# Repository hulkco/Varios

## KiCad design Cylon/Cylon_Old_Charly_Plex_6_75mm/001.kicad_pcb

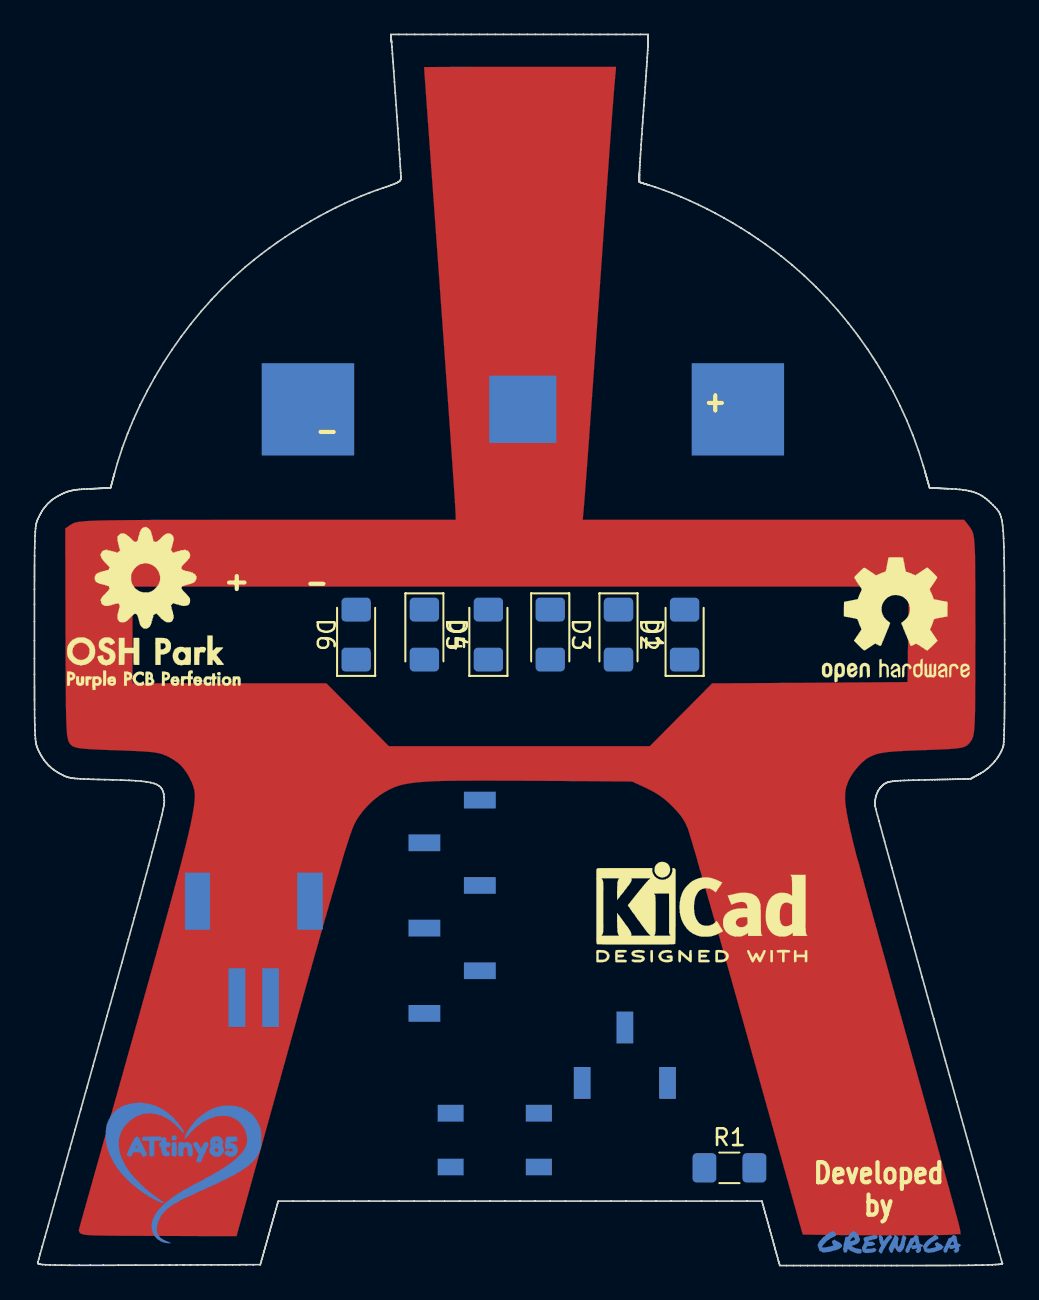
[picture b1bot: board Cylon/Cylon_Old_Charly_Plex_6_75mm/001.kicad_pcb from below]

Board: 2 copper layers, 57.8 x 73.3 mm, 17 parts (15 on the bottom side), 6 nets, no tracks yet.

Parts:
BT1: Battery_Cell; S8211R
D1, D2, D3, D4, D5, D6: LED; LED_1206_3216Metric_Pad1.42x1.75mm_HandSolder
J1: Conn_01x02; JST-S2B-PH-SM4-TB
J2: Conn_01x06_x03; Digispark_SMD_Reverse
R1: R_Small; R_1206_3216Metric_Pad1.42x1.75mm_HandSolder
SW2: SW_Push_Dual; SW_Push_PTS647_4.5mm
U1: PCB; Cylon_001
U2: Firma; firma_Cu_Mask
U3: Oshpark_logo; OSHpark-1-1200
U4: Oshpark_Purple; OSHpark-2-1800
U5: OSHW_Silk; OSHW-Logo2_9.8x8mm_SilkScreen
U6: Love_ATtiny85; Moon_ATtiny85

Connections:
/PB_0: D1.1, D2.2, D5.1, D6.2, J2.1
/PB_1: D1.2, D2.1, D3.1, D4.2, J2.2
/PB_2: J2.3, R1.1, SW2.1, SW2.2
/PB_4: D3.2, D4.1, D5.2, D6.1, J2.5
GND: BT1.2, J1.2, J2.8, SW2.3, SW2.4
VCC: BT1.1, J1.1, J2.9, R1.2

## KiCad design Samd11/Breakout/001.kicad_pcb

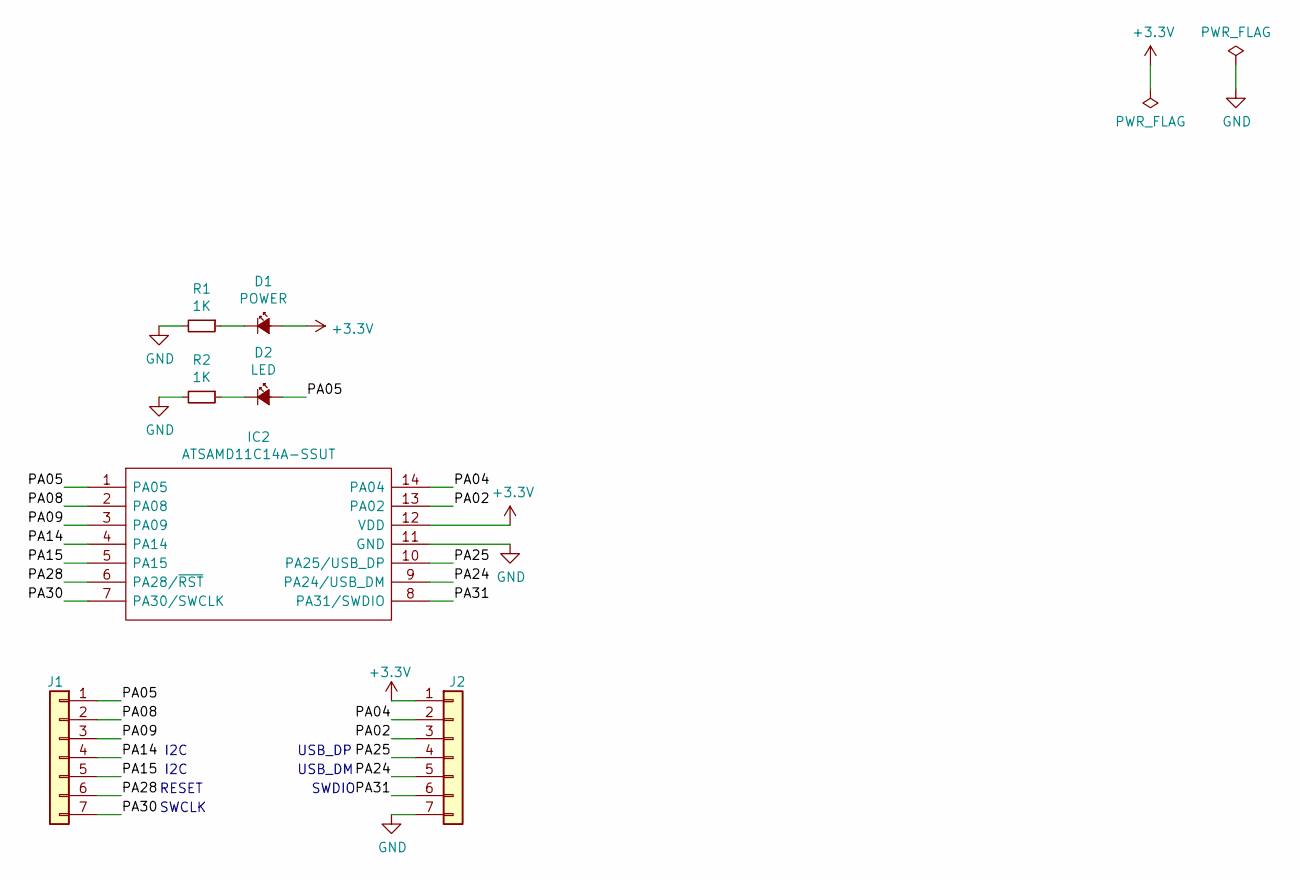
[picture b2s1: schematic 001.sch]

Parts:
D1: POWER; LED_1206_3216Metric_Pad1.42x1.75mm_HandSolder
D2: LED; LED_1206_3216Metric_Pad1.42x1.75mm_HandSolder
IC2: ATSAMD11C14A-SSUT; SOIC127P600X175-14N; Mouser Part Number 556-ATSAMD11C14ASSUT
J1, J2: Conn_01x07; PinHeader_1x07_P2.54mm_Vertical
R1, R2: 1K; R_1206_3216Metric_Pad1.42x1.75mm_HandSolder

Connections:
+3V3: D1.2 (A), IC2.12 (VDD), J2.1
/PA02: IC2.13 (PA02), J2.3
/PA04: IC2.14 (PA04), J2.2
/PA05: D2.2 (A), IC2.1 (PA05), J1.1
/PA08: IC2.2 (PA08), J1.2
/PA09: IC2.3 (PA09), J1.3
/PA14: IC2.4 (PA14), J1.4
/PA15: IC2.5 (PA15), J1.5
/PA24: IC2.9 (PA24/USB_DM), J2.5
/PA25: IC2.10 (PA25/USB_DP), J2.4
/PA28: IC2.6 (PA28/~RST), J1.6
/PA30: IC2.7 (PA30/SWCLK), J1.7
/PA31: IC2.8 (PA31/SWDIO), J2.6
GND: IC2.11 (GND), J2.7, R1.2, R2.2
unnamed: D1.1 (K), R1.1
unnamed: D2.1 (K), R2.1

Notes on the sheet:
SWDIO
SWCLK
RESET
I2C
USB_DM
USB_DP

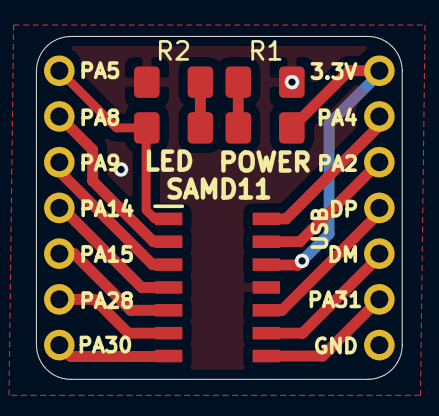
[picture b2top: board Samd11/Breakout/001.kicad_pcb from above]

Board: 2 copper layers, 20.3 x 19.0 mm, 7 parts (0 on the bottom side), 16 nets.

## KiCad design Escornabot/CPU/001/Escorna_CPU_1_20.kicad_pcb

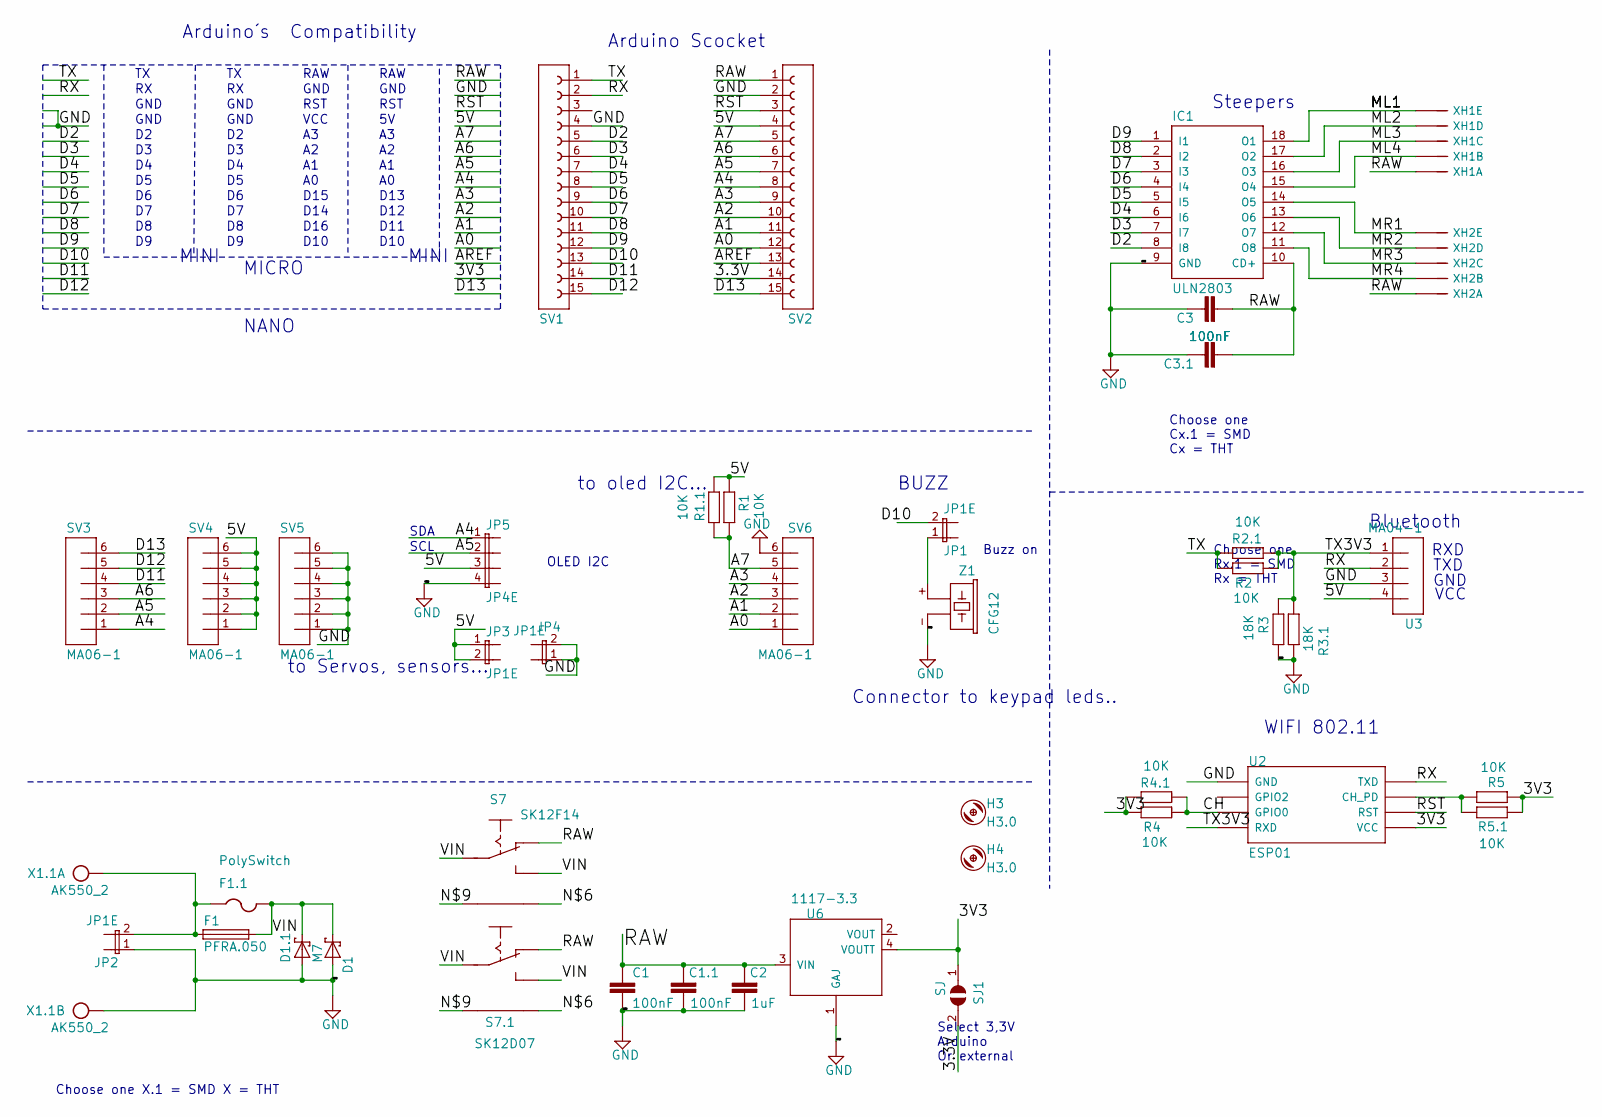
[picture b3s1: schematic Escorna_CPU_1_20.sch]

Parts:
C1, C3: 100nF; C025-025X050
C1.1, C3.1: 100nF; C0603K
C2: 1uF; C1206K
D1: 1N5817; DO41-10
D1.1: M7; SMA-DO214AC
F1: PFRA.050; TE5
F1.1: PolySwitch; R1206
H3, H4: H3.0; 3,0
IC1: ULN2803; DIL18
JP1, JP2: JP1E; 1X02
JP3, JP4: JP1E; JP1
JP5: JP4E; JP4
R1, R2, R4, R5: 10K; 0204_7
R1.1, R2.1, R4.1, R5.1: 10K; R0603
R3: 18K; 0204_7
R3.1: 18K; R0603
S7: SK12F14; ESCORNA_SK-12F14-G
S7.1: SK12D07; ESCORNA_SK-12D07
SJ1: SJ
SV1, SV2: 1x15 SOCKET STRIP; CON-LSTA_FE15
SV3, SV4, SV5, SV6: MA06-1
U2: ESP01
U3: MA04-1
U6: 1117-3.3; SOT223
X1.1: AK550_2
XH1, XH2: B5B-XH-A
Z1: CFG12; F_CM12P

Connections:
/3.3V: SJ1.2, SV2.14
/3V3: R4.1, R4.1.1, R5.1, R5.1.1, SJ1.1, U2.VCC, U6.4 (VOUTT)
/5V: JP3.1, JP3.2, JP5.3, R1.1, R1.1.1, SV2.4, SV4.1, SV4.2, SV4.3, SV4.4, SV4.5, SV4.6, U3.4
/A0: SV2.12, SV6.1
/A1: SV2.11, SV6.2
/A2: SV2.10, SV6.3
/A3: SV2.9, SV6.4
/A4: JP5.1, SV2.8, SV3.1
/A5: JP5.2, SV2.7, SV3.2
/A6: SV2.6, SV3.3
/A7: R1.2, R1.1.2, SV2.5, SV6.5
/CH: R4.2, R4.1.2, U2.GPIO0
/D2: IC1.8 (I8), SV1.5
/D3: IC1.7 (I7), SV1.6
/D4: IC1.6 (I6), SV1.7
/D5: IC1.5 (I5), SV1.8
/D6: IC1.4 (I4), SV1.9
/D7: IC1.3 (I3), SV1.10
/D8: IC1.2 (I2), SV1.11
/D9: IC1.1 (I1), SV1.12
/D10: JP1.2, SV1.13
/D11: SV1.14, SV3.4
/D12: SV1.15, SV3.5
/D13: SV2.15, SV3.6
/ML1: IC1.18 (O1), XH1.P$5
/ML2: IC1.17 (O2), XH1.P$4
/ML3: IC1.16 (O3), XH1.P$3
/ML4: IC1.15 (O4), XH1.P$2
/MR1: IC1.14 (O5), XH2.P$5
/MR2: IC1.13 (O6), XH2.P$4
/MR3: IC1.12 (O7), XH2.P$3
/MR4: IC1.11 (O8), XH2.P$2
/N$6: S7.P$5, S7.1.P$5
/N$9: S7.P$4, S7.1.P$4
/RAW: C1.1, C1.1.2, C2.2, C3.2, C3.1.2, IC1.10 (CD+), S7.P$2 (O), S7.1.P$2 (O), SV2.1, U6.3 (VIN), XH1.P$1, XH2.P$1
/RST: SV2.3, U2.RST
/RX: SV1.2, U2.TX (TXD), U3.2
/TX: R2.1, R2.1.1, SV1.1
/TX3V3: R2.2, R2.1.2, R3.1, R3.1.2, U2.RX (RXD), U3.1
/VIN: D1.C, D1.1.K (C), F1.2, F1.1.2, S7.P$1, S7.P$3 (S), S7.1.P$1, S7.1.P$3 (S)
GND: C1.2, C1.1.1, C2.1, C3.1, C3.1.1, D1.A, D1.1.A, IC1.9 (GND), JP2.1, JP4.1, JP4.2, JP5.4, R3.2, R3.1.1, SV1.4, SV2.2, SV5.1, SV5.2, SV5.3, SV5.4, SV5.5, SV5.6, SV6.6, U2.GND, U3.3, U6.1 (GAJ), X1.1.2, Z1.- (2)
unnamed: F1.1, F1.1.1, JP2.2, X1.1.1
unnamed: JP1.1, Z1.+ (1)
unnamed: R5.2, R5.1.2, U2.CH_PD

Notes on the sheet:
Arduino Scocket
Steepers
BUZZ
Bluetooth
RXD
TXD
GND
VCC
Buzz on
NANO
Arduino´s Compatibility
MINI
MICRO
RAW
RST
D13
D15
D12
D14
D11
D16
D10
WIFI 802.11
Choose one X.1 = SMD X = THT
Choose one Cx.1 = SMD Cx = THT
SCL
SDA
OLED I2C
Choose one Rx.1 = SMD Rx = THT
Select 3,3V Arduino Or external
Connector to keypad leds..
to oled I2C...
to Servos, sensors...

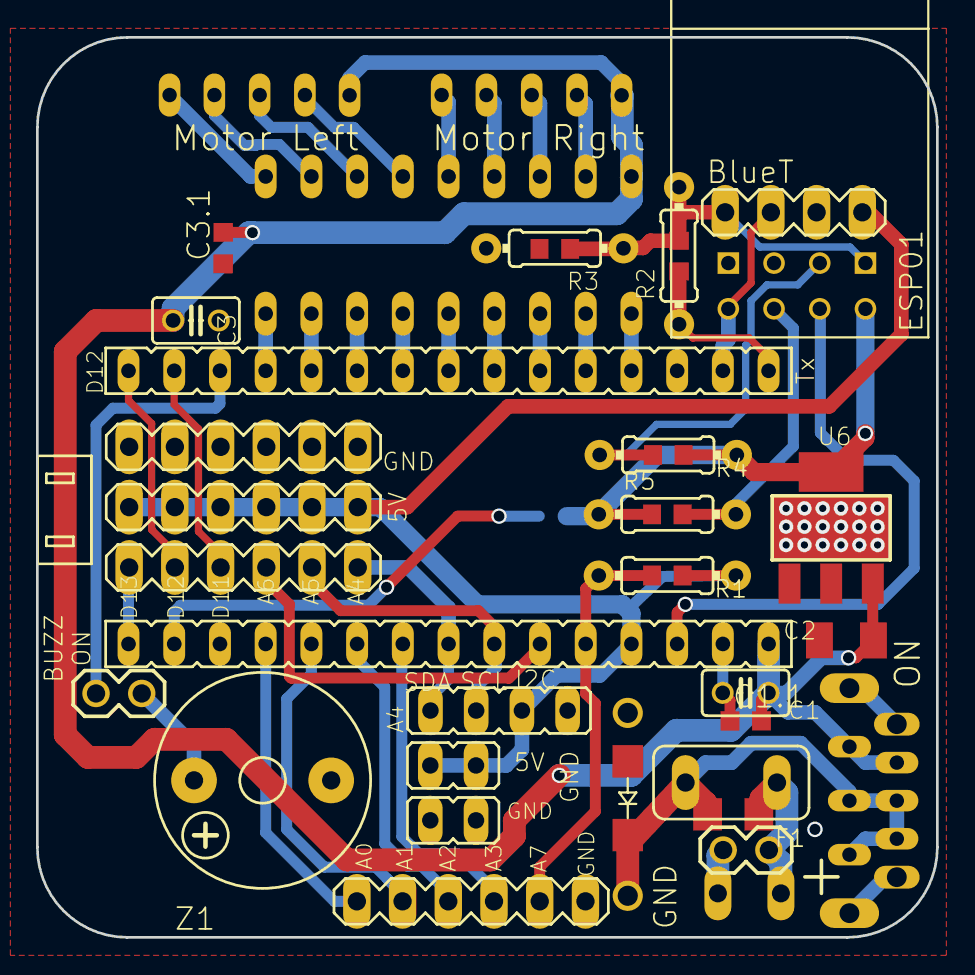
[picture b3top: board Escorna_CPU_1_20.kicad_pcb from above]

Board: 2 copper layers, 50.0 x 50.0 mm, 41 parts (0 on the bottom side), 44 nets.

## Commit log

2018-12-07 Firts Upload
2018-12-07 Some updates
2018-12-08 Add SVGs
2018-12-10 Orange upload
2018-12-14 Updates Constitution
2018-12-14 Update Constitution
2019-01-09 Add new repos
2019-01-16 Add some updates
2019-01-16 New Mazbasica
2019-01-17 some changes mazbasica
2019-01-17 Add Logo
2019-01-23 Add Updates Neo Reverse
2019-02-08 Udpate Links ESP8266
2019-04-21 Uptade HG Badge
2019-05-03 Add Flash Breakout and Nast Shield
2019-05-03 Updates Flash
2019-05-07 minor updates TFT-Breakout
2019-05-07 Add Pi Hat
2019-05-13 Minor updates
2019-05-22 Add Escorni_Badge
2019-05-22 Update SVG
2019-05-24 Add Draw settings in Docs TFT
2019-05-28 Add images to Escorni_Badge
2019-05-29 Add HCC Module
2019-05-29 Update image escornabot
2019-05-30 Add Gemas
2019-06-11 Add DJ Cat
2019-06-14 Add TFT Shield
2019-06-14 Add Docs
2019-06-15 Add some changess & 3d model
2019-06-15 Update 3d Model
2019-06-16 Add Bast Shield
2019-06-16 Various updates
2019-07-10 Add TFT footprints
2019-07-11 Some minors updates
2019-07-14 Add Material Curso Verano 2019
2019-07-18 Changes Curso Verano 2019
2019-08-06 Push MF-Jalisco Badge
2019-08-17 add attiny85 Wereable project
2019-08-18 Add Battery Holder & 3d Straw Hat
    Battery Holder WA-BCMC and Straw Hat Led
2019-08-19 add attiny85 Wearable project
2019-08-20 Some changes
2019-08-20 Add Round
2019-08-21 Add KiCad Template
2019-08-22 Add BreadBoard Template
2019-08-25 Update Escorni
2019-08-26 Update Escorni Badge
2019-08-28 Add Regla de Leds
2019-08-29 Add Maz-ONE
2019-08-30 Escorni NANO update
2019-09-03 Add 3d model
2019-09-05 Add some minors changes
2019-09-06 Add some Art Work
2019-09-27 Add MF Rome Badge
2019-09-28 Add Buzzers info
2019-09-29 Add Moon Reverse Led Kit
2019-09-30 Add route trace
2019-09-30 Moonlight soldering Kit Updates
2019-10-01 Minor changes MoonLigth
2019-10-01 Check
2019-10-12 Changes Regla
2019-10-12 Add Digispark Footprint
2019-10-14 Add info
2019-10-15 UpdateMoon
2019-10-15 Changes Moon
2019-10-16 Add Attiny85 Breakout
2019-10-18 Add Heart Logo
2019-10-21 Add Cylon Badge
2019-10-21 Add Cylon New Version
2019-10-23 Add MoonMaker PCB
2019-10-23 Add some Agora Course changes
2019-10-31 Add NANO template
2019-11-05 Add agora Pin 2032
2019-11-05 Remove Agora Pin 2032
2019-11-11 Agora Code
2019-11-13 Add 0805 moon badge
2019-12-22 Add new Atiny85 & SAMD11 Breakout
2019-12-31 New_Install_SO_Update
2020-01-08 Update
    Minor changes
2020-01-08 Update Mouser footprints
2020-01-08 Add Nordic Module
2020-01-09 Add Tuto nRF52840
2020-01-11 Update Docs nRF52xxx
2020-01-14 Add the Key
2020-01-14 Update nRF52840 module
2020-01-16 Add MS88SF2
2020-01-18 Some minor updates to Feather to Nano
2020-01-22 updates en cache de kicad
2020-01-24 Add copy SVG
2020-01-28 Add Star Shield Nano
2020-02-03 Add Pines
2020-02-04 Add New NANO Badge
2020-02-05 delete
2020-02-09 Add Nano to Feather w-lipo
2020-03-19 Add Lober Badge
2020-03-20 Update lober
2020-04-22 test kikit
2021-04-08 Add gitignore
2021-04-08 Update gitignore
2021-05-16 Minor changes
